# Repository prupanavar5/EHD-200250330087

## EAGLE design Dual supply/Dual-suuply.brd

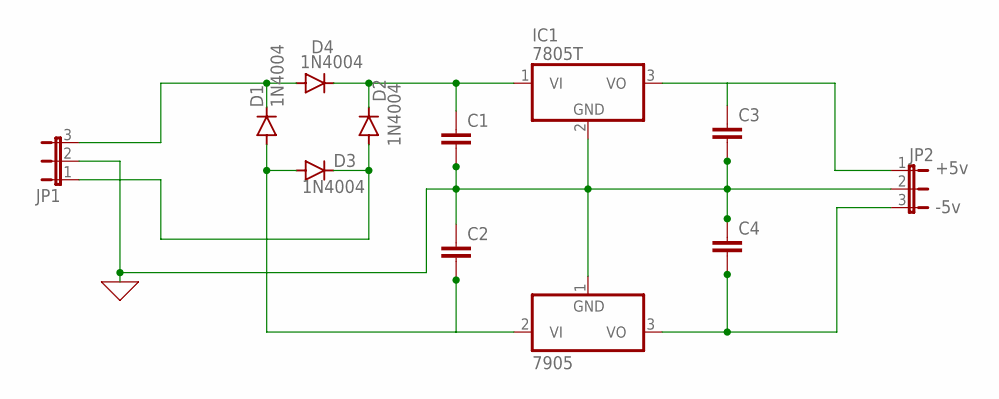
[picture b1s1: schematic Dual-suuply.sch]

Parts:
7905: 7906T; TO220H
C1, C2, C3, C4: C-EU025-024X044; C025-024X044
D1, D2, D3, D4: 1N4004; DO41-10
IC1: 7805T; TO220H
JP1, JP2: JP2E; JP2

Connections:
0: 7905.1 (GND), C1.2, C2.1, C3.2, C4.1, IC1.2 (GND), JP1.2, JP2.2
unnamed: D1.C, D4.A, JP1.3
unnamed: C1.1, D2.C, D4.C, IC1.1 (VI)
unnamed: C3.1, IC1.3 (VO), JP2.1
unnamed: D2.A, D3.C, JP1.1
unnamed: 7905.3 (VO), C4.2, JP2.3
unnamed: 7905.2 (VI), C2.2, D1.A, D3.A

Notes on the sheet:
+5v
-5v

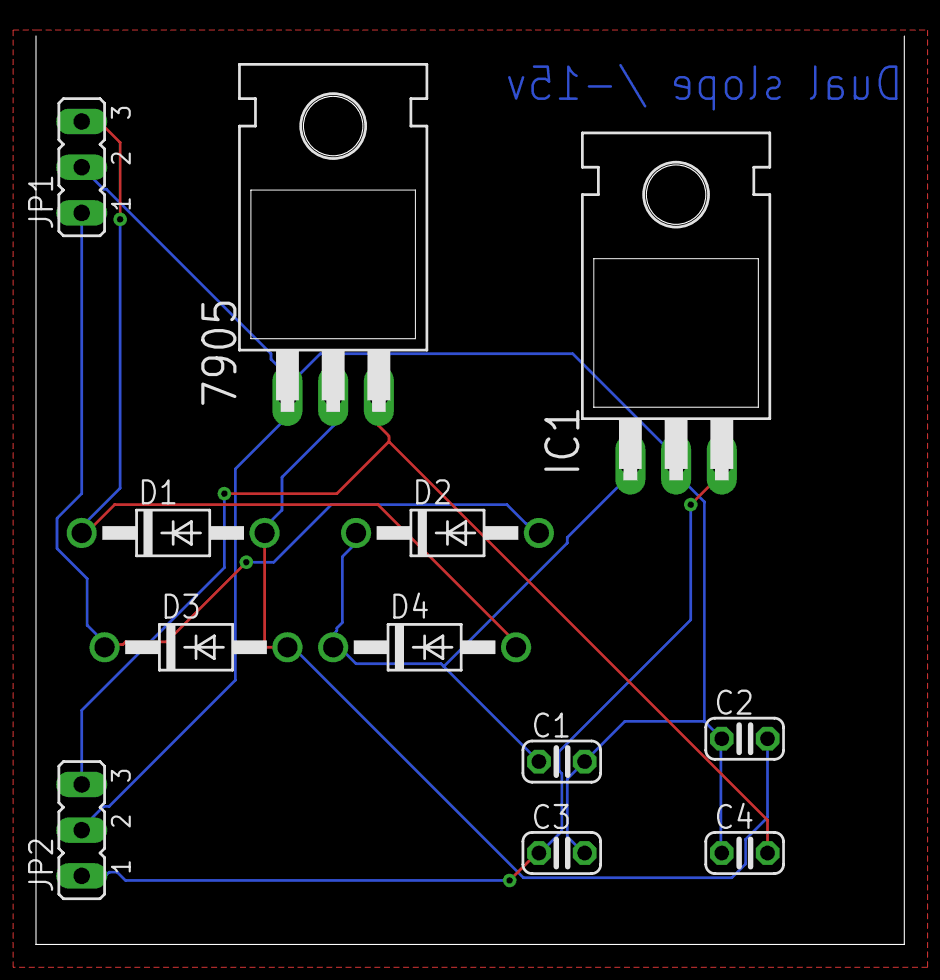
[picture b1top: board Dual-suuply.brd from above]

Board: 2 copper layers, 48.2 x 50.5 mm, 12 parts (0 on the bottom side), 7 nets.

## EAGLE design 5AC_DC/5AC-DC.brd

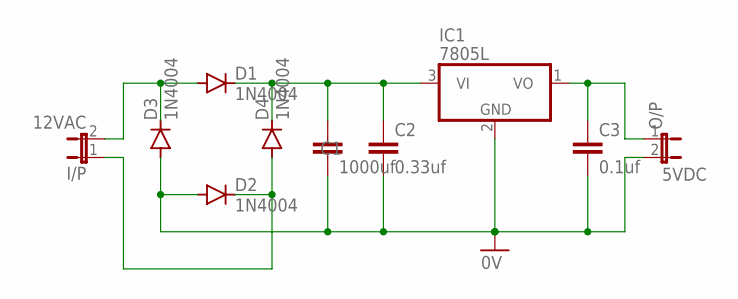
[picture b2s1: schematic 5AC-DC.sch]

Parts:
C1: 1000uf; C2.5-3
C2: 0.33uf; C2.5-3
C3: 0.1uf; C2.5-3
D1, D2, D3, D4: 1N4004; DO41-10
I/P: 12VAC; JP1
IC1: 7805L; TO92
O/P: 5VDC; JP1

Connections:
0V: C1.2, C2.2, C3.2, D2.A, D3.A, IC1.2 (GND), O/P.2
unnamed: D1.A, D3.C, I/P.2
unnamed: C1.1, C2.1, D1.C, D4.C, IC1.3 (VI)
unnamed: D2.C, D4.A, I/P.1
unnamed: C3.1, IC1.1 (VO), O/P.1

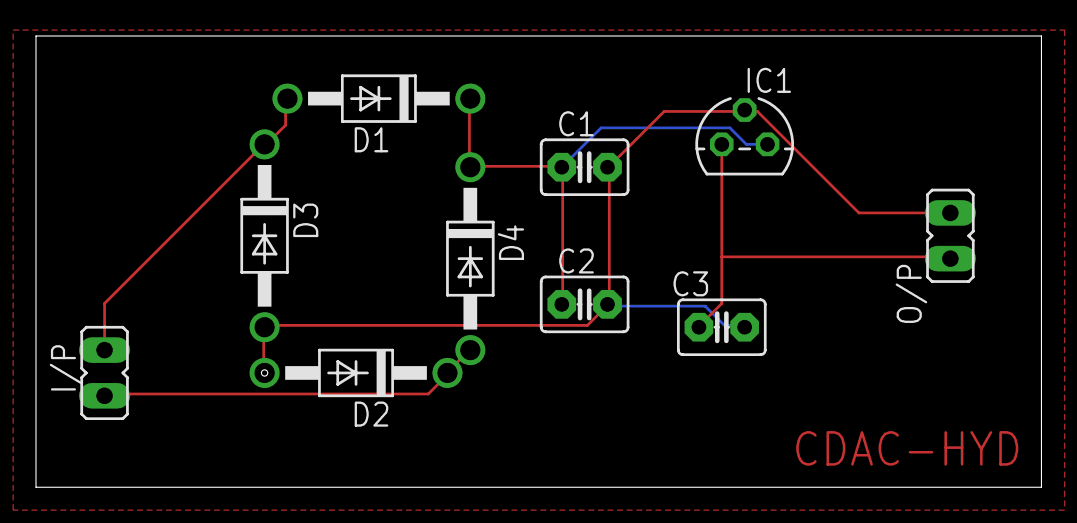
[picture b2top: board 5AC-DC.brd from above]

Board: 2 copper layers, 55.9 x 25.1 mm, 10 parts (0 on the bottom side), 5 nets.

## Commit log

2020-09-30 My very firs commit
2020-10-03 library
2020-10-18 Dual power supply board
